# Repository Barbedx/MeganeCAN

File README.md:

# MeganeCAN

ESP32-based CAN-bus companion for Renault Megane 2 infotainment displays.

Connects an **ESP32** to the car CAN bus and acts as a smart sidecar: renders custom menus and text on the OEM display, bridges phone media controls via Bluetooth (Apple Media Service or BLE Keyboard), exposes a web UI for live configuration, and supports OTA firmware updates. Optional ELM327/OBD diagnostics via WiFi.

🇺🇦 When you use this project, you automatically support Ukraine.

> ⚠️ Safety: hobby project for off-road / testing use. Do not interact with menus while driving.

---

## Features

| Category | Details |
|---|---|
| **CAN bus** | 500 Kbps, GPIO 3 (RX) / GPIO 4 (TX). Listens to OEM frames and replies to sync/ack. |
| **Display** | Emulates the head-unit radio over ISO-TP-style CAN to drive the OEM display. Two radio protocols: **Carminat** (large monochrome display only) and **UpdateList** (both the monochrome `updatelist_menu` and the 8-segment `updatelist`). |
| **Bluetooth** | AMS mode: advertises as a **BLE peripheral** — the iPhone pairs from Settings → Bluetooth, then the ESP reads now-playing (AMS), notifications (ANCS) and clock (CTS) as a GATT client over that link. Keyboard mode: BLE HID peripheral. |
| **Web UI** | PsychicHttp async server on port 80. Configure display type, BT mode, text, time. |
| **OTA** | ElegantOTA at `/update`. |
| **Diagnostics** | ELM327 over WiFi STA (V-LINK adapter). Queries ECUs and exposes JSON at `/api/live`. |

---

## Hardware

Minimum:
- **ESP32-C3** (or ESP32) development board
- **CAN transceiver** — SN65HVD230 / TJA1050 / MCP2551
- Wiring to CAN-H, CAN-L, GND, and a fused 5 V supply

> Do **not** add a second 120 Ω terminator if the bus is already terminated.

Pinout (ESP32-C3):

| Signal | GPIO |
|---|---|
| CAN RX | 3 |
| CAN TX | 4 |

---

## Architecture

### Class diagram

```
IDisplay  (pure virtual interface)
│  tick(), recv(), processEvents()
│  setText(), setState(), setTime()
│  showMenu(), ProcessKey(), onKeyPressed()
│
└── AffaDisplayBase  (abstract — ISO-TP CAN send engine)
      │  affa3_send() / affa3_do_send()
      │  funcs[] array  (registered CAN function IDs + ack state)
      │  _sync_status   (FAILED | PEER_ALIVE | START | FUNCSREG)
      │  setMediaInfo()  — virtual no-op, overridden by subclasses
      │  tickMedia()     — virtual no-op, overridden by subclasses
      │  setKeyHandler() — installs the key callback
      │
      ├── Affa2Base  (Affa2 CAN protocol — basic text, fallback default)
      │     funcs: { 0x121 SETTEXT, 0x1B1 DISPLAY_CTRL }
      │     sync ping: 0x3DF   filler: 0x81
      │     │
      │     ├── Affa2Display      (8-segment — adds media title scroll)
      │     │     + setMediaInfo()  builds "Artist - Title" string
      │     │     + tickMedia()     scrolls 8-char window every 400 ms
      │     │
      │     └── Affa2MenuDisplay  (full-LED — stub, same CAN protocol)
      │
      └── Affa3NavDisplay  (Affa3Nav "Carminat" — full nav display)
            funcs: { 0x151 SETTEXT/CTRL, 0x1F1 NAV }
            sync ping: 0x3AF   filler: 0x00
            + showMenu() / highlightItem() / showInfoMenu()
            + setMediaInfo() — renders full media screen
            + tickMedia()    — scrolls title (18-char window)
            + Menu system (mainMenu, key handling, NVS-backed BT items)
```

### Main loop data flow

```
 ┌──────────┐   CAN frame   ┌──────────────────┐
 │ CAN bus  │ ────────────► │ gotFrame()        │
 └──────────┘               │ → display->recv() │
                            └──────────────────┘

 ┌───────────────┐  MediaInformation  ┌─────────────────────────┐
 │ BLE / AMS     │ ─────────────────► │ onDataUpdateCallback()  │
 │ (iPhone)      │                    │ → display->setMediaInfo()│
 └───────────────┘                    └─────────────────────────┘

 loop()
   ├── serialCommands.ReadSerial()
   ├── ElegantOTA.loop()
   ├── Bluetooth::Service()          (AMS mode)
   ├── display->tickMedia()          (non-blocking scroll)
   ├── auto-time sync via CTS        (AMS mode, once per connection)
   ├── display->processEvents()
   └── elmManager->tick()            (OBD, when WiFi connected)
```

### BT key mapping

| Physical key | AMS action | BLE Keyboard HID |
|---|---|---|
| Pause | TogglePlayPause | KEY_MEDIA_PLAY_PAUSE |
| RollUp | NextTrack | KEY_MEDIA_NEXT_TRACK |
| RollDown | PreviousTrack | KEY_MEDIA_PREVIOUS_TRACK |
| VolumeUp (hold) | VolumeUp ×15 | KEY_MEDIA_VOLUME_UP |

---

## CAN packet IDs

### Affa2 protocol (Affa2Base / Affa2Display / Affa2MenuDisplay)

| Constant | ID | Direction | Purpose |
|---|---|---|---|
| `PACKET_ID_SYNC` | `0x3DF` | ESP32 → display | Alive ping |
| `PACKET_ID_SYNC_REPLY` | `0x3CF` | display → ESP32 | Sync ack |
| `PACKET_ID_SETTEXT` | `0x121` | ESP32 → display | Set text |
| `PACKET_ID_DISPLAY_CTRL` | `0x1B1` | ESP32 → display | Enable (0x02) / Disable (0x00) |
| `PACKET_ID_KEYPRESSED` | `0x0A9` | display → ESP32 | Key press event |
| `PACKET_REPLY_FLAG` | `0x400` | — | OR-mask on ID for ack frames |
| `PACKET_FILLER` | `0x81` | — | Padding byte |

### Affa3Nav (Carminat)

| Constant | ID | Direction | Purpose |
|---|---|---|---|
| `PACKET_ID_SYNC` | `0x3AF` | ESP32 → display | Alive ping |
| `PACKET_ID_SYNC_REPLY` | `0x3CF` | display → ESP32 | Sync ack |
| `PACKET_ID_SETTEXT` / `DISPLAY_CTRL` | `0x151` | ESP32 → display | Text + enable/disable (same ID, different payload) |
| `PACKET_ID_NAV` | `0x1F1` | ESP32 → display | Menu / nav data |
| `PACKET_ID_KEYPRESSED` | `0x1C1` | display → ESP32 | Key press event |
| `PACKET_FILLER` | `0x00` | — | Padding byte |

Scroll lock indicator byte (Affa3Nav `showMenu`):

| Value | Meaning |
|---|---|
| `0x00` | No scroll arrows |
| `0x07` | Scroll up arrow |
| `0x0B` | Scroll down arrow |
| `0x0C` | Both arrows |

---

## Display types

Selected via NVS key `config/display_type`. Takes effect after restart.

| NVS value | Class | Notes |
|---|---|---|
| `carminat` *(default)* | `CarminatDisplay` | Carminat protocol → **large monochrome** display: full media screen + interactive menu + notification popups |
| `updatelist_menu` | `UpdateListMenuDisplay` | UpdateList protocol → **monochrome LCD** (menu); extends `UpdateListDisplay` |
| `updatelist` | `UpdateListDisplay` | UpdateList protocol → **8-segment** display; scrolls "Artist - Title" (8-char window, 400 ms/step) via AMS |
| *(other / unset)* | `UpdateListBase` | UpdateList protocol base — fallback |

> Note: older docs/sections below may still use the pre-rename class names
> (`Affa2*`/`Affa3Nav*`) and values (`affa2`/`affa3`). The authoritative model is
> the matrix above and `CLAUDE.md`.

---

## NVS configuration keys

| Namespace | Key | Type | Default | Values |
|---|---|---|---|---|
| `config` | `display_type` | String | `affa3nav` | `affa2` / `affa2menu` / `affa3` / `affa3nav` |
| `config` | `bt_mode` | String | `ams` | `ams` / `keyboard` |
| `config` | `auto_time` | Bool | `true` | Sync display clock from phone via CTS |
| `display` | `autoRestore` | Bool | `false` | Restore last text on boot |
| `display` | `lastText` | String | — | Last text shown (restored on boot) |
| `display` | `welcomeText` | String | — | Scroll on boot (overrides default) |

---

## Build & flash

```bash
# Build
pio run

# Flash over USB
pio run -t upload

# Serial monitor (115200 baud)
pio device monitor

# Build + flash in one step
pio run -t upload && pio device monitor
```

Target: `esp32-c3-devkitm-1` (see `platformio.ini`).

### WiFi / secrets

Edit `src/secrets.h` (not tracked by git):

```cpp
#define Soft_AP_WIFI_SSID "MeganeCAN"
#define Soft_AP_WIFI_PASS "yourpassword"
```

The file is ignored via:

```bash
git update-index --assume-unchanged src/secrets.h
```

---

## Web UI (`http://<device-ip>/`)

| Route | Method | Purpose |
|---|---|---|
| `/` | GET | Main configuration page |
| `/setDisplay` | POST | Set display type, restarts ESP32 |
| `/setbtmode` | POST | Set BT mode + auto_time, restarts ESP32 |
| `/config/restore` | GET | Read (`?enable` absent) or write (`?enable=1/0`) auto-restore flag |
| `/static` | GET | Show static text (`?text=`, `?save` to persist) |
| `/scroll` | GET | Scroll text (`?text=`, `?save` to save as welcome) |
| `/settime` | GET | Set display clock (`?time=HHMM`) |
| `/setVoltage` | GET | Debug voltage override |
| `/getdisplaytype` | GET | Returns current NVS display_type string |
| `/getbtmode` | GET | Returns current NVS bt_mode string |
| `/getautotime` | GET | Returns `1` or `0` |
| `/getlasttext` | GET | Returns last saved text |
| `/getwelcometext` | GET | Returns saved welcome text |
| `/api/live` | GET | ELM327 diagnostic snapshot JSON |
| `/affa3/setMenu` | GET | Send menu frame (`?caption=`, `?name1=`, `?name2=`, `?scrollLock=`) |
| `/affa3test` | GET | Affa3 display test page |
| `/emulate` | GET | Button emulation page |
| `/emulate/key` | POST | Inject a key press (`?key=`, `?hold=`) |
| `/update` | GET | ElegantOTA firmware upload |

---

## Serial commands (115200 baud)

| Command | Example | Effect |
|---|---|---|
| `e` | `e` | Enable display |
| `d` | `d` | Disable display |
| `st <HHMM>` | `st 1430` | Set display clock |
| `msr <text> [delay_ms]` | `msr HELLO 300` | Scroll text right |
| `msl <text> [delay_ms]` | `msl MEGANE 250` | Scroll text left |

---

## ELM327 / OBD diagnostics

> **Note:** ELM327 connection is currently disabled in firmware (`connectToElm()` is commented out). The infrastructure is complete but needs WiFi STA / BLE coexistence tuning before re-enabling.

WiFi STA connects to `V-LINK` (open network, TCP `192.168.0.10:35000`). Cycles through PID plans querying:

| CAN header | ECU |
|---|---|
| `7E0` | Engine |
| `743` | Gearbox / transmission |
| `744` | HVAC |
| `745` | Additional |
| `74D` | Gearbox / alternator |

Results exposed at `GET /api/live` as JSON. To add a PID plan: create `PidPlan_XXX.h` and register it in `buildCombinedPlan()` inside `MyELMManager.h`.

---

## Source layout

```
src/
├── main.cpp                    — setup(), loop(), HandleKey(), initDisplay()
├── apple_media_service.cpp/.h  — BLE AMS client (NimBLE)
├── bluetooth.cpp/.h            — BLE scan + connect + CTS
├── current_time_service.cpp/.h — BLE Current Time Service (clock sync)
├── secrets.h                   — WiFi credentials (not tracked)
│
├── display/
│   ├── IDisplay.h              — pure virtual display interface
│   ├── AffaDisplayBase.cpp/.h  — ISO-TP CAN engine, sync state machine
│   ├── AffaCommonConstants.h   — shared enums (AffaKey, AffaError, SyncStatus…)
│   │
│   ├── Affa2/
│   │   ├── Affa2Constants.h         — Affa2 CAN packet IDs + namespace
│   │   ├── Affa2Base.cpp/.h         — Affa2 protocol implementation (base class)
│   │   ├── Affa2Display.h/.cpp      — 8-segment variant, Spotify title scroll
│   │   └── Affa2MenuDisplay.h       — full-LED variant stub
│   │
│   └── Affa3Nav/
│       ├── Affa3NavConstants.h
│       ├── Affa3NavDisplay.cpp/.h   — full media screen + menu system
│       ├── AuxModeTracker.cpp/.h
│       └── Menu/
│           ├── Menu.cpp/.h          — hierarchical menu (Field, List, MultiField)
│
├── commands/
│   └── DisplayCommands.cpp/.h  — HTTP command dispatch layer
│
├── effects/
│   └── ScrollEffect.h          — blocking scroll helper (boot / serial)
│
├── server/
│   └── HttpServerManager.cpp/.h — PsychicHttp routes + HTML page
│
├── utils/
│   ├── AffaDebug.h
│   └── CanUtils.cpp/.h         — CAN frame send helpers
│
└── ElmManager/
    ├── MyELMManager.h/.cpp     — ELM327 TCP session + PID cycling
    ├── DiagPlanCommon.h        — MetricDef, PidPlan types
    └── PidPlan_*.h             — per-ECU PID definitions
```

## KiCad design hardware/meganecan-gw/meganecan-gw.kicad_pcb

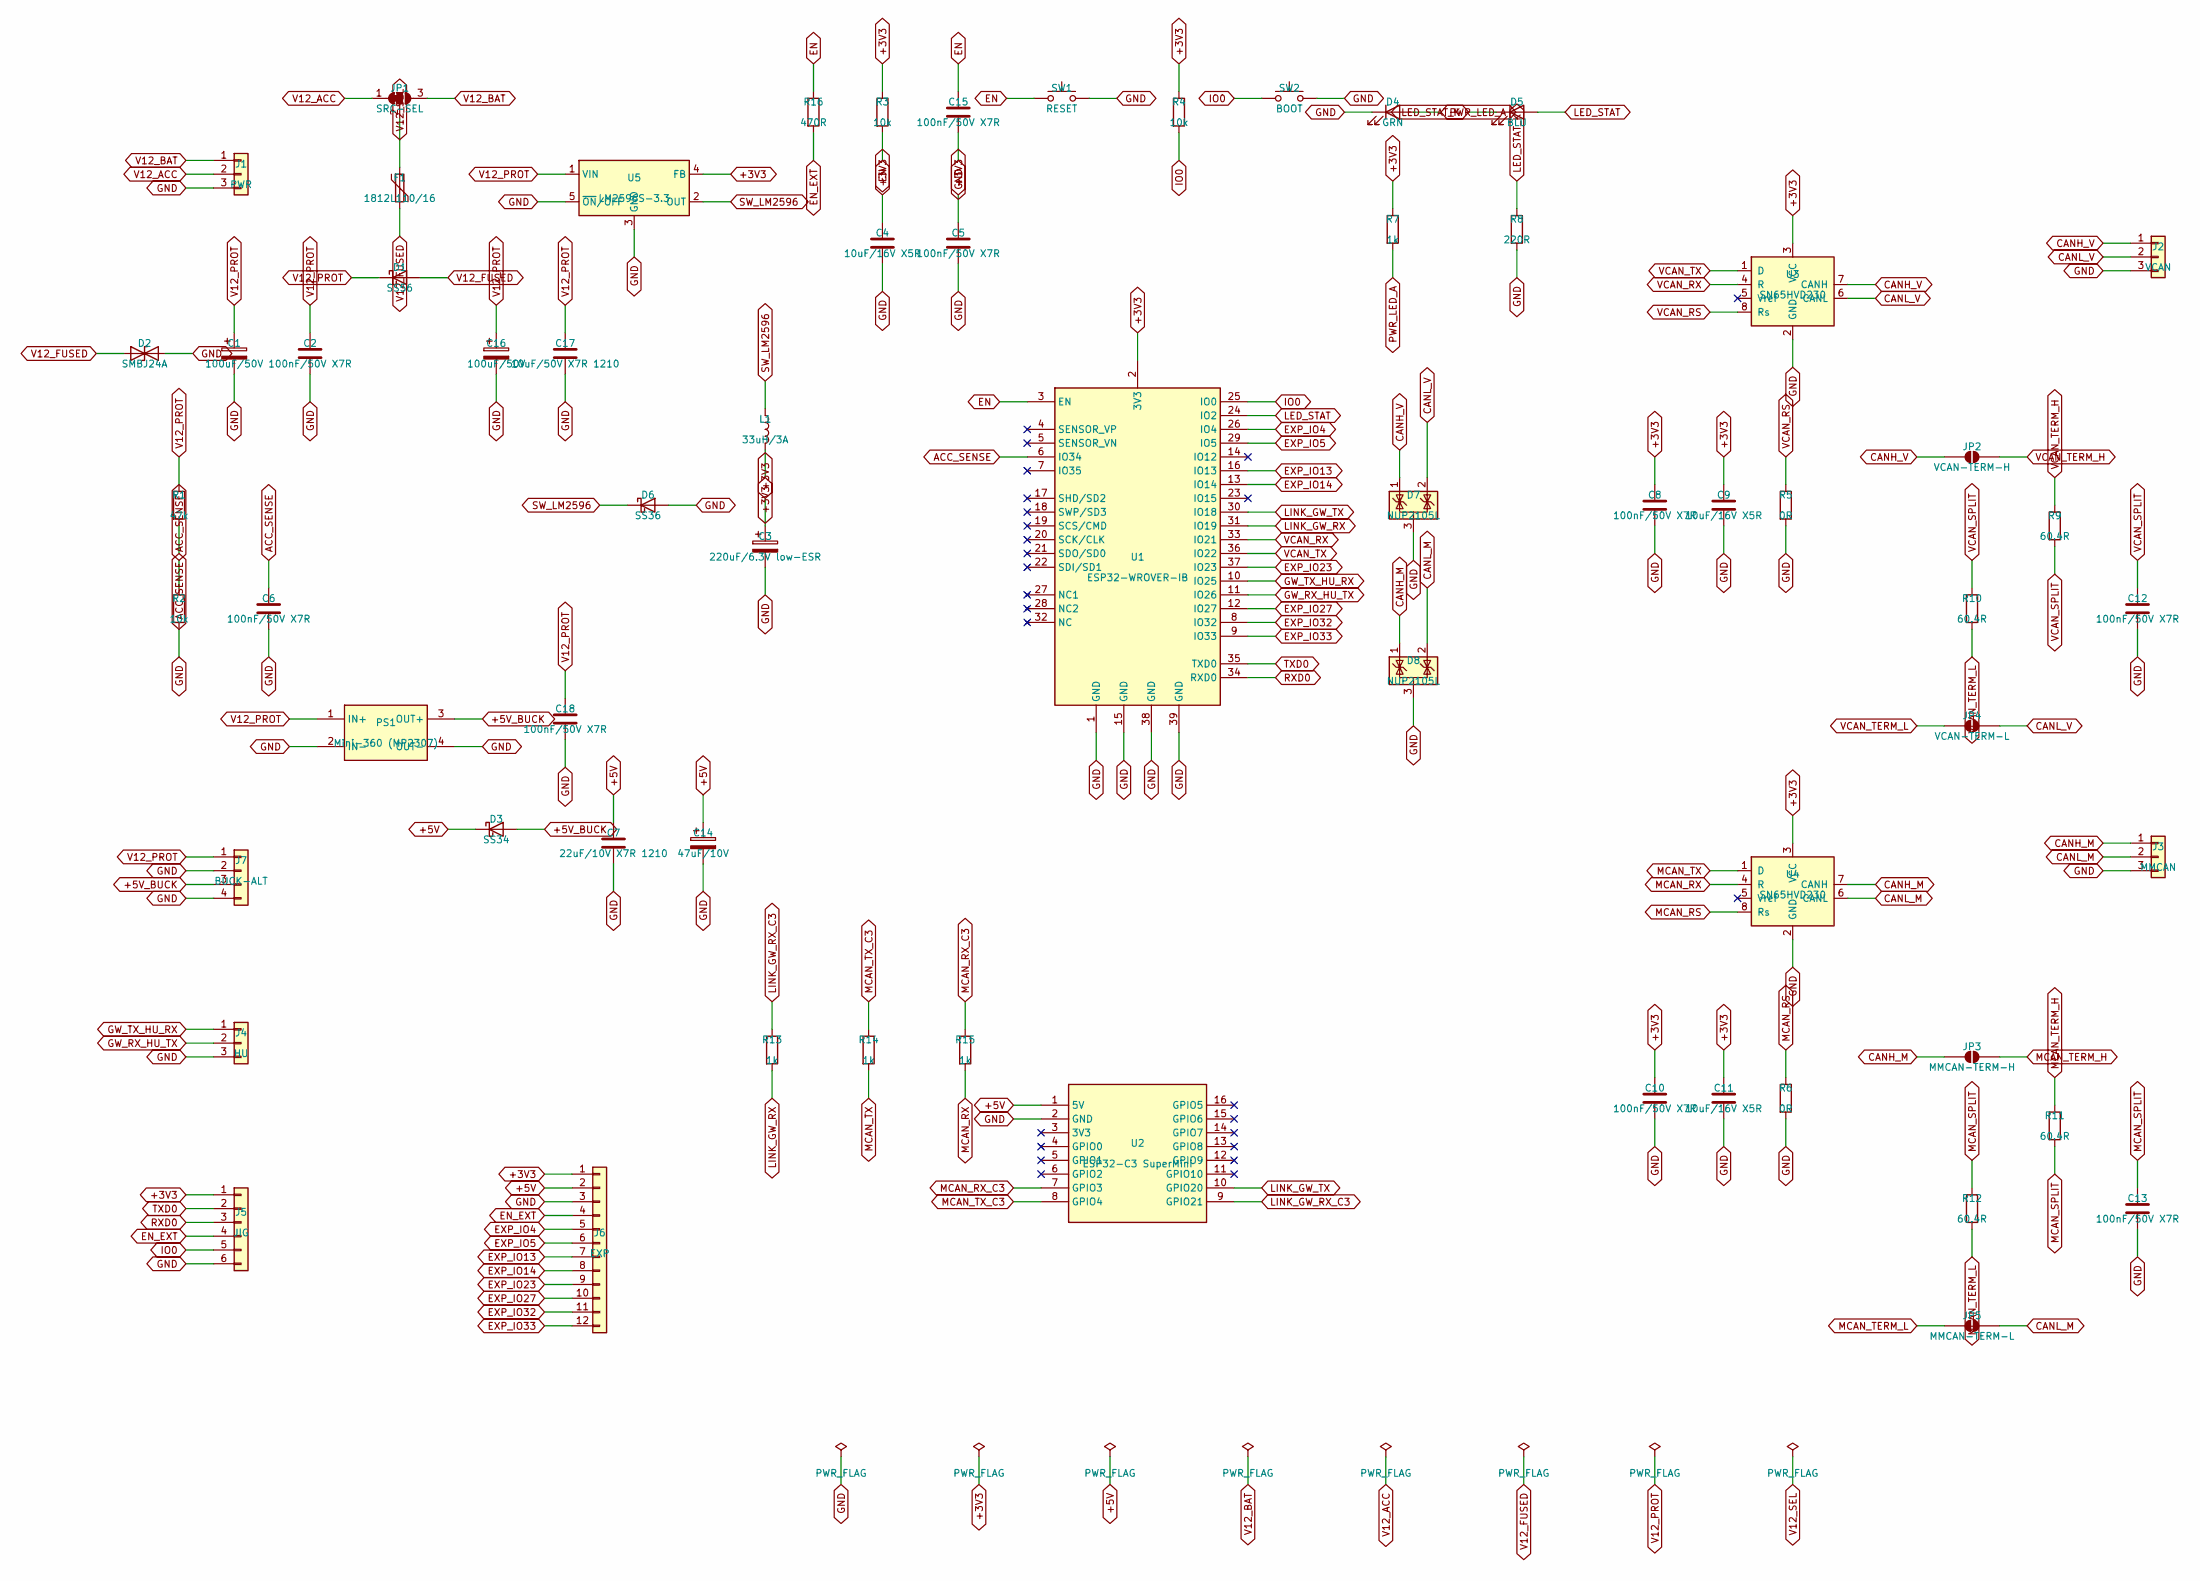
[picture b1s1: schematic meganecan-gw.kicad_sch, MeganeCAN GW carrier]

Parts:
C1, C16: 100uF/50V; CP_Radial_D10.0mm_P5.00mm; LCSC C3013
C2, C5, C6, C8, C10, C12, C13, C15, C18: 100nF/50V X7R; C_0805_2012Metric_Pad1.18x1.45mm_HandSolder; LCSC C1590
C3: 220uF/6.3V low-ESR; CP_Radial_D6.3mm_P2.50mm; LCSC C3020
C4, C9, C11: 10uF/16V X5R; C_0805_2012Metric_Pad1.18x1.45mm_HandSolder; LCSC C15850
C7: 22uF/10V X7R 1210; C_1210_3225Metric_Pad1.33x2.70mm_HandSolder; LCSC C29823
C14: 47uF/10V; CP_Radial_D5.0mm_P2.00mm; LCSC C3020
C17: 10uF/50V X7R 1210; C_1210_3225Metric_Pad1.33x2.70mm_HandSolder
D1: SS56; D_SMA-SMB_Universal_Handsoldering
D2: SMBJ24A; D_SMB_Handsoldering; LCSC C2687123
D3: SS34; D_SMA-SMB_Universal_Handsoldering; LCSC C8678
D4: GRN; LED_0805_2012Metric_Pad1.15x1.40mm_HandSolder; LCSC C2297
D5: BLU; LED_0805_2012Metric_Pad1.15x1.40mm_HandSolder; LCSC C2293
D6: SS36; D_SMA-SMB_Universal_Handsoldering
D7, D8: NUP2105L; SOT-23
F1: 1812L110/16; Fuse_1812_4532Metric_Pad1.30x3.40mm_HandSolder; LCSC C2830175
J1: PWR; TerminalBlock_Phoenix_MKDS-1,5-3-5.08_1x03_P5.08mm_Horizont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
J2: VCAN; TerminalBlock_Phoenix_MKDS-1,5-3-5.08_1x03_P5.08mm_Horizont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
J3: MMCAN; TerminalBlock_Phoenix_MKDS-1,5-3-5.08_1x03_P5.08mm_Horizont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
J4: HU; JST_XH_B3B-XH-A_1x03_P2.50mm_Vertical
J5: JIG; PinHeader_1x06_P2.54mm_Vertical
J6: EXP; PinHeader_1x12_P2.54mm_Vertical
J7: BUCK-ALT; PinHeader_1x04_P2.54mm_Vertical
JP1: SRC-SEL; SolderJumper-3_P1.3mm_Bridged12_RoundedPad1.0x1.5mm
JP2: VCAN-TERM-H; SolderJumper-2_P1.3mm_Open_RoundedPad1.0x1.5mm
JP3: MMCAN-TERM-H; SolderJumper-2_P1.3mm_Open_RoundedPad1.0x1.5mm
JP4: VCAN-TERM-L; SolderJumper-2_P1.3mm_Open_RoundedPad1.0x1.5mm
JP5: MMCAN-TERM-L; SolderJumper-2_P1.3mm_Open_RoundedPad1.0x1.5mm
L1: 33uH/3A; L_12x12mm_H8mm; LCSC C169305
PS1: Mini-360 (MP2307); MINI360_4pad_Socket
R1: 47k; R_0805_2012Metric_Pad1.20x1.40mm_HandSolder; LCSC C17714
R2, R3, R4: 10k; R_0805_2012Metric_Pad1.20x1.40mm_HandSolder; LCSC C17414
R5, R6: 0R; R_0805_2012Metric_Pad1.20x1.40mm_HandSolder
R7, R13, R14, R15: 1k; R_0805_2012Metric_Pad1.20x1.40mm_HandSolder; LCSC C17513
R8: 220R; R_0805_2012Metric_Pad1.20x1.40mm_HandSolder
R9, R10, R11, R12: 60.4R; R_0805_2012Metric_Pad1.20x1.40mm_HandSolder; LCSC C22980
R16: 470R; R_0805_2012Metric_Pad1.20x1.40mm_HandSolder
SW1: RESET; SW_PUSH_6mm; LCSC C393939
SW2: BOOT; SW_PUSH_6mm; LCSC C393939
U1: ESP32-WROVER-IB
U2: ESP32-C3 SuperMini; MODULE_ESP32-C3-SUPERMINI
U3, U4: SN65HVD230; SOIC-8_3.9x4.9mm_P1.27mm; LCSC C12084
U5: LM2596S-3.3; TO-263-5_TabPin3; LCSC C347421

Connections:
+3V3: C3.1, C4.1, C5.1, C8.1, C9.1, C10.1, C11.1, J5.1, J6.1, L1.2, R3.1, R4.1, R7.1, U1.2 (3V3), U3.3 (VCC), U4.3 (VCC), U5.4 (FB)
+5V: C7.1, C14.1, D3.1 (K), J6.2, U2.1 (5V)
+5V_BUCK: D3.2 (A), J7.3, PS1.3 (OUT+)
ACC_SENSE: C6.1, R1.2, R2.1, U1.6 (IO34)
CANH_M: D8.1 (K), J3.1, JP3.1 (A), U4.7 (CANH)
CANH_V: D7.1 (K), J2.1, JP2.1 (A), U3.7 (CANH)
CANL_M: D8.2 (K), J3.2, JP5.2 (B), U4.6 (CANL)
CANL_V: D7.2 (K), J2.2, JP4.2 (B), U3.6 (CANL)
EN: C15.1, R3.2, R16.1, SW1.1, U1.3 (EN)
EN_EXT: J5.4, J6.4, R16.2
EXP_IO4: J6.5, U1.26 (IO4)
EXP_IO5: J6.6, U1.29 (IO5)
EXP_IO13: J6.7, U1.16 (IO13)
EXP_IO14: J6.8, U1.13 (IO14)
EXP_IO23: J6.9, U1.37 (IO23)
EXP_IO27: J6.10, U1.12 (IO27)
EXP_IO32: J6.11, U1.8 (IO32)
EXP_IO33: J6.12, U1.9 (IO33)
GND: C1.2, C2.2, C3.2, C4.2, C5.2, C6.2, C7.2, C8.2, C9.2, C10.2, C11.2, C12.2, C13.2, C14.2, C15.2, C16.2, C17.2, C18.2, D2.2 (A2), D4.1 (K), D6.2 (A), D7.3 (A), D8.3 (A), J1.3, J2.3, J3.3, J4.3, J5.6, J6.3, J7.2, J7.4, PS1.2 (IN-), PS1.4 (OUT-), R2.2, R5.2, R6.2, R8.2, SW1.2, SW2.2, U1.1 (GND), U1.15 (GND), U1.38 (GND), U1.39 (GND), U2.2 (GND), U3.2 (GND), U4.2 (GND), U5.3 (GND), U5.5 (~ON/OFF)
GW_RX_HU_TX: J4.2, U1.11 (IO26)
GW_TX_HU_RX: J4.1, U1.10 (IO25)
IO0: J5.5, R4.2, SW2.1, U1.25 (IO0)
LED_STAT: D5.2 (A), U1.24 (IO2)
LED_STAT_K: D5.1 (K), R8.1
LINK_GW_RX: R13.2, U1.31 (IO19)
LINK_GW_RX_C3: R13.1, U2.9 (GPIO21)
LINK_GW_TX: U1.30 (IO18), U2.10 (GPIO20)
MCAN_RS: R6.1, U4.8 (Rs)
MCAN_RX: R15.2, U4.4 (R)
MCAN_RX_C3: R15.1, U2.7 (GPIO3)
MCAN_SPLIT: C13.1, R11.2, R12.1
MCAN_TERM_H: JP3.2 (B), R11.1
MCAN_TERM_L: JP5.1 (A), R12.2
MCAN_TX: R14.2, U4.1 (D)
MCAN_TX_C3: R14.1, U2.8 (GPIO4)
PWR_LED_A: D4.2 (A), R7.2
RXD0: J5.3, U1.34 (RXD0)
SW_LM2596: D6.1 (K), L1.1, U5.2 (OUT)
TXD0: J5.2, U1.35 (TXD0)
V12_ACC: J1.2, JP1.1 (A)
V12_BAT: J1.1, JP1.3 (B)
V12_FUSED: D1.2 (A), D2.1 (A1), F1.2
V12_PROT: C1.1, C2.1, C16.1, C17.1, C18.1, D1.1 (K), J7.1, PS1.1 (IN+), R1.1, U5.1 (VIN)
V12_SEL: F1.1, JP1.2 (C)
VCAN_RS: R5.1, U3.8 (Rs)
VCAN_RX: U1.33 (IO21), U3.4 (R)
VCAN_SPLIT: C12.1, R9.2, R10.1
VCAN_TERM_H: JP2.2 (B), R9.1
VCAN_TERM_L: JP4.1 (A), R10.2
VCAN_TX: U1.36 (IO22), U3.1 (D)

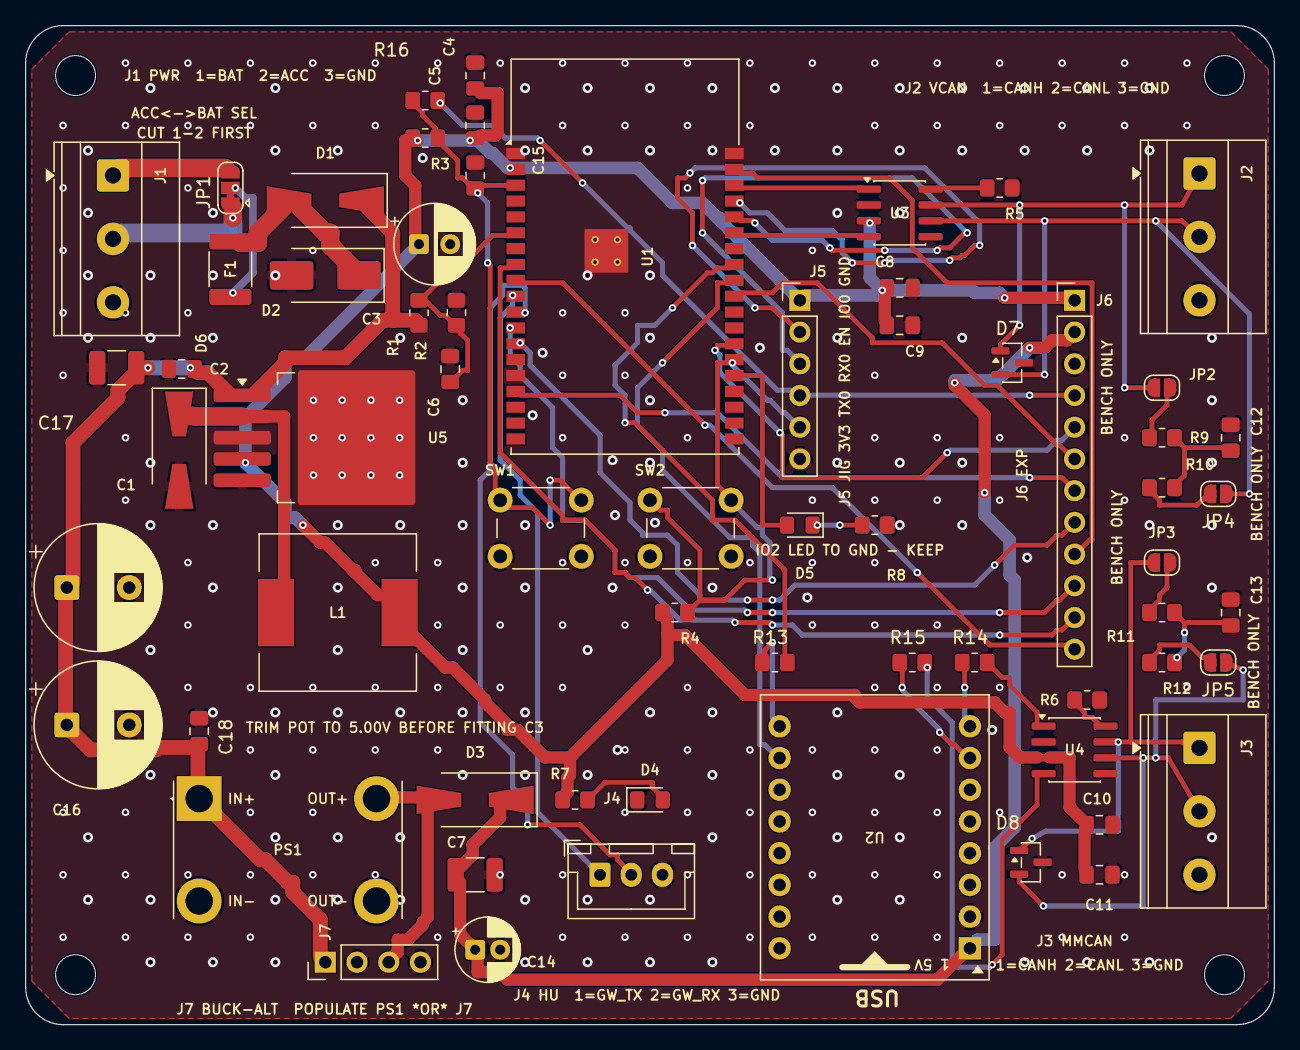
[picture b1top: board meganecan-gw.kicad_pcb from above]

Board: 2 copper layers, 100.0 x 80.0 mm, 68 parts (0 on the bottom side), 50 nets.

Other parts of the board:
H1, H2, H3, H4: MountingHole_3.2mm_M3

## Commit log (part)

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2025-04-02 added BT
2025-04-10 chaos but works
2025-04-14 authorization solvaed
2025-04-14 aborts
2025-04-15 all done
2025-04-15 clearing
2025-04-15 fixes
2025-04-15 add library
2025-04-15 all works finally
2025-04-15 some more fixes
2025-04-16 add voltage
2025-04-16 refactor
2025-04-16 add secrets
2025-06-23 builded
2025-06-24 refactor a bit
2025-06-24 remove old code
2025-06-24 something
2025-06-25 affa3.c is correct
2025-06-25 refactoring
2025-07-02 refactoring+mini
2025-07-18 a lot of refactoring in progress
2025-07-27 som refactoring, fixing menu (not builidng tbh)
2025-07-27 refactoring build add settings
2025-08-04 final
2025-08-04 add Ota build succeed not tested
2025-08-15 more difrent thjings
2025-08-18 real
2025-08-18 some strange fixes again
2025-08-18 switch ru rd
2025-08-20 add notes
2025-08-20 clear
2025-08-20 menuactivetracker
2025-08-21 ELM MANAGER
2025-08-21 ok FIX
2025-08-25 some changes refactoring in progresss
2025-08-26 fucking elm session opener
2025-08-26 devssss
2025-08-27 addlogs
2025-08-27 fix named typo in PidPlan filename
2025-08-27 back log filter
2025-08-27 more compleated version
2025-08-27 fixz buildfed
2025-08-28 add corect filters (working, unstable)
2025-09-02 add initi
2025-09-02 fix display
2025-11-15 change bt to ams
2025-11-15 lenght
2025-11-15 elm testing
2025-11-16 some small fixes
2025-11-16 fix buttons
2025-11-16 auto volume max
2026-02-12 Initialize README with project overview and setup
    Add detailed project description and features for MeganeCAN.
2026-02-12 Refine README time sync description
    Removed redundant wording in README about syncing time.
2026-02-12 Update README to specify ESP32 power supply provision
    Clarify that ESP32 boards usually provide the dedicated power supply.
2026-02-27 Consolidate BT key handling into main.cpp HandleKey
    Both modes (AMS and BleKeyboard) do the same thing for the same keys —
    only the transport differs. Put them side by side in one function:
    HandleKey: btMode=="ams" → AppleMediaService commands
    btMode=="keyboard" → bleKeyboard.write()
    - bleKeyboard object moved to main.cpp (next to HandleKey)
    - setKeyHandler(HandleKey) always called regardless of mode
2026-02-28 Rename Affa3Display to Affa2Base, fix Affa2 key handling, add ELM/display integration
    - Rename src/display/Affa3/ → src/display/Affa2/, class Affa3Display → Affa2Base,
    namespace Affa3 → Affa2, constants file Affa3Constants.h → Affa2Constants.h
    - Fix Affa2Base::recv() to properly extract key bytes and push to queue;
    previously keys were silently dropped and never dispatched to AMS/keyboard
    - Add processEvents() to Affa2Base to drain the key queue each loop tick
    - Add virtual onElmUpdate(key, value) to AffaDisplayBase; implement in
2026-02-28 Redesign BT scanning with candidate list, NVS persistence, and device cycling
    - Remove hardcoded iPhone manufacturer prefix and Spotify UUID filter
    - Collect all Apple (company ID 0x004C) connectable devices into a candidate
    list (up to 8 entries) with deduplication
    - Save preferred device address to NVS on successful AMS connection; auto-select
    and connect to it on subsequent scans without user interaction
    - Add SelectNext()/SelectPrev() to cycle through discovered candidates using
2026-02-28 Update README with correct class hierarchy and new features
    - Fix class diagram to show true 2-level inheritance:
    Affa2Base → Affa2Display / Affa2MenuDisplay, AffaDisplayBase → Affa3NavDisplay
    - Update display types table to reflect actual 3 display options
    - Document BT mode (AMS vs keyboard), ELM enable toggle, and new BT cycling UX
    - Update source layout section to show Affa2/ directory structure
2026-03-01 Refactor BT state machine, fix scan blocking, add candidate web UI
    Replace BeginDone/TargetFound/Connected bools with explicit BtState
    enum (IDLE/SCANNING/CONNECTING/CONNECTED). Fix root cause of Service()
    doing nothing: state=SCANNING now set before scan->start() so the
    loop runs even while the bg task is blocked inside scan->start(0,0).
    Also: dedup skip-log, RSSI+type in candidates, Try button in web UI,
    BT init in 16 KB background task, menu/aux-mode fixes.
2026-03-01 Migrate to NimBLE 2.x, add server+client AMS pattern and BLE keyboard mode
    - Replace ESP32-BLE-Keyboard + NimBLE 1.x with NimBLE 2.x only
    - Add BleMediaKeyboard.h: minimal NimBLE 2.x HID consumer-control keyboard
    (play/pause, next/prev, volume — replaces the external library)
    - Add dual BT mode: 'ams' (Apple Media Service) or 'keyboard' (HID),
    selected from NVS key config/bt_mode
    - bluetooth.cpp: add BLE server+client pattern for AMS
2026-03-02 Simplify BT: bonding=false, Spotify UUID only, drop RSSI fallback
    - Restore simple connect-on-Spotify-UUID logic from origin/BT
    - bonding=false fixes err=13 (BLE_HS_EPREEMPTED) caused by privacy layer rebuilding HCI resolving list
    - Remove RSSI fallback that was connecting to neighbours' phones
    - Add serial commands pp/nx/pv for play-pause/next/prev
2026-03-02 Fix AMS display bugs, re-enable ELM via NVS, add clock to media header
    - Re-enable ELM manager via NVS (elm_enabled key, default false)
    - Add ELM enabled/WiFi connect logs that fire once (static bool guards)
    - Fix _scrollPos reset on track change (was resetting unused _mediaScrollPos)
    - Fix header string precedence bug in renderMediaScreen (ternary operator)
    - Remove dead _mediaScrollPos field from header
    - Add right-aligned [HH:MM] clock to Spotify screen header, truncates
2026-03-02 Fix BLE init order on ESP32-C3: start NimBLE before softAP
    On ESP32-C3 (single radio), starting softAP before NimBLE init causes the
    AP beacon traffic to block BLE stack registration with the coexistence manager.
    Move xTaskCreate(BLE init) before WiFi.softAP() so the radio is free during
    NimBLE startup — matches the working pattern from the BT branch.
2026-03-04 add origin work refs
2026-03-05 fix: complete skip_funcreg to suppress all sync/reply/registration in radio mode
    - Guard recv() PACKET_ID_SYNC_REPLY block with _skipFuncReg so the ESP32
    never sends sync replies (0x70/0xB0) when the radio owns the session
    - Replace dead answerNeeded flag with !_skipFuncReg guard — same intent,
    no dangling TODO variable
    - Add AFFA3_PRINT logs throughout sync path and affa3_send skip branch
    - Revert force_aux (_forceAuxMode field, setters, NVS load in main.cpp) —
2026-03-05 fix: relax AUX detection to prefix match, drop trailing-spaces requirement
    Checking only text[1..3] == 'AUX' is sufficient; trailing content varies
    by radio firmware and broke detection on some units.
2026-03-05 feat: add fullSnapshotJson endpoint and live OBD table in web UI
    - MyELMManager::fullSnapshotJson() returns all metrics with name,
    shortName, label, unit, value, hasValue fields as a JSON array
    - GET /api/live/full serves the full snapshot
    - Web UI main page replaces the plain /api/live link with an auto-refreshing
    table (2s interval) showing all metrics with current values and units
2026-03-12 buuilds, uploads
2026-03-13 spmething
2026-03-13 some refactoring by codex
2026-03-13 Add ESP-IDF target and stabilize BT/WiFi handoff
2026-03-13 Stabilize BT/WiFi coexistence and media info
2026-03-13 Tune A2DP coexistence and startup noise
2026-03-13 Refactor display handshake and queued CAN runtime
2026-06-16 chore: .gitattributes — normalize line endings to LF
    Stops the recurring "LF will be replaced by CRLF" warnings on every commit by storing
    LF in the repo (native checkout on Windows). Binary asset types marked binary.
2026-06-16 #3: extract /diag + /affa3test inline pages to headers
    Move the two remaining inline PROGMEM HTML literals out of HttpServerManager.cpp
    (685 -> 612 lines) into DiagPage.h (DIAG_PAGE) and Affa3TestPage.h (AFFA3TEST_PAGE),
    mirroring DashboardPage.h/WirePage.h. The handlers keep a local `page` pointer aimed
    at the constant, so the reply lines are unchanged. Behavior-neutral; esp32dev builds.
2026-06-16 refactor: extract WS command handler into console/WireConsole
    Move wireCommand (@INJ/@EMU/@KEY from a WireLink) out of main.cpp into
    console/WireConsole, parallel to SerialConsole. main registers
    WireProto::onCommand(WireConsole::handle, nullptr). Behavior-neutral; esp32dev builds.
2026-06-16 framework: static EventBus + IModule lifecycle (roadmap 5-6, research-informed)
    - src/core/EventBus.{h,cpp}: typed, statically-sized pub/sub for cross-feature signals
    (BT state, AUX, screen-changed). Fixed slots, no heap, no std::function (function
    pointer + ctx) — the ETL etl::observer style the framework research recommends. For
    genuine N×M fan-out only; hot CAN frames stay on direct calls.
    - src/core/IModule.h: uniform feature lifecycle (begin/service/name) for the App
    composition root.
2026-06-16 docs: morning report — autonomous framework session summary
    What got done overnight (radio-send host-test keystone, CI, HttpServerManager slimming,
    WireConsole, deep-research fold, EventBus+IModule), verification status (native 24/24,
    both builds, bench-verified), the push blocker, and the ranked remaining roadmap with
    why each item was/wasn't done unattended.
2026-06-16 docs: CarminatDisplay decomposition plan (coordinator + collaborators)
    Target skeleton for splitting the 1146-line monolith: a thin coordinator that owns the
    panel driver (AFFA3 transport + screen builders) and delegates features to clean
    collaborators (NowPlaying = media+notif, MenuController = menu+nav, DiagController = ELM)
    that depend only on a small ICarminatPanel port — unit-testable against a fake panel and
    swappable for a future Android-radio panel. Ordered, low-risk-first, each step
    behavior-preserving + verified on the real panel.
2026-06-16 docs: finalize CarminatDisplay decomposition plan (coupling map + step plan)
    Map the file-global coupling (AuxModeTracker tracker, eventQueue/Event, mainMenu.isActive)
    that intertwines recv + keys + media, define NowPlaying(IDisplay&, AuxModeTracker&, Menu&)
    with refs not std::function, and give the exact 3-step extraction order (NowPlaying ->
    MenuController -> DiagController) with per-step on-panel verification. The panel driver +
    sync state machine stay in CarminatDisplay (that IS the Carminat panel).
2026-06-16 understand anything things
2026-06-16 latest commit may be bad
2026-06-16 some fixes from car
2026-06-16 fix ino cnfg
